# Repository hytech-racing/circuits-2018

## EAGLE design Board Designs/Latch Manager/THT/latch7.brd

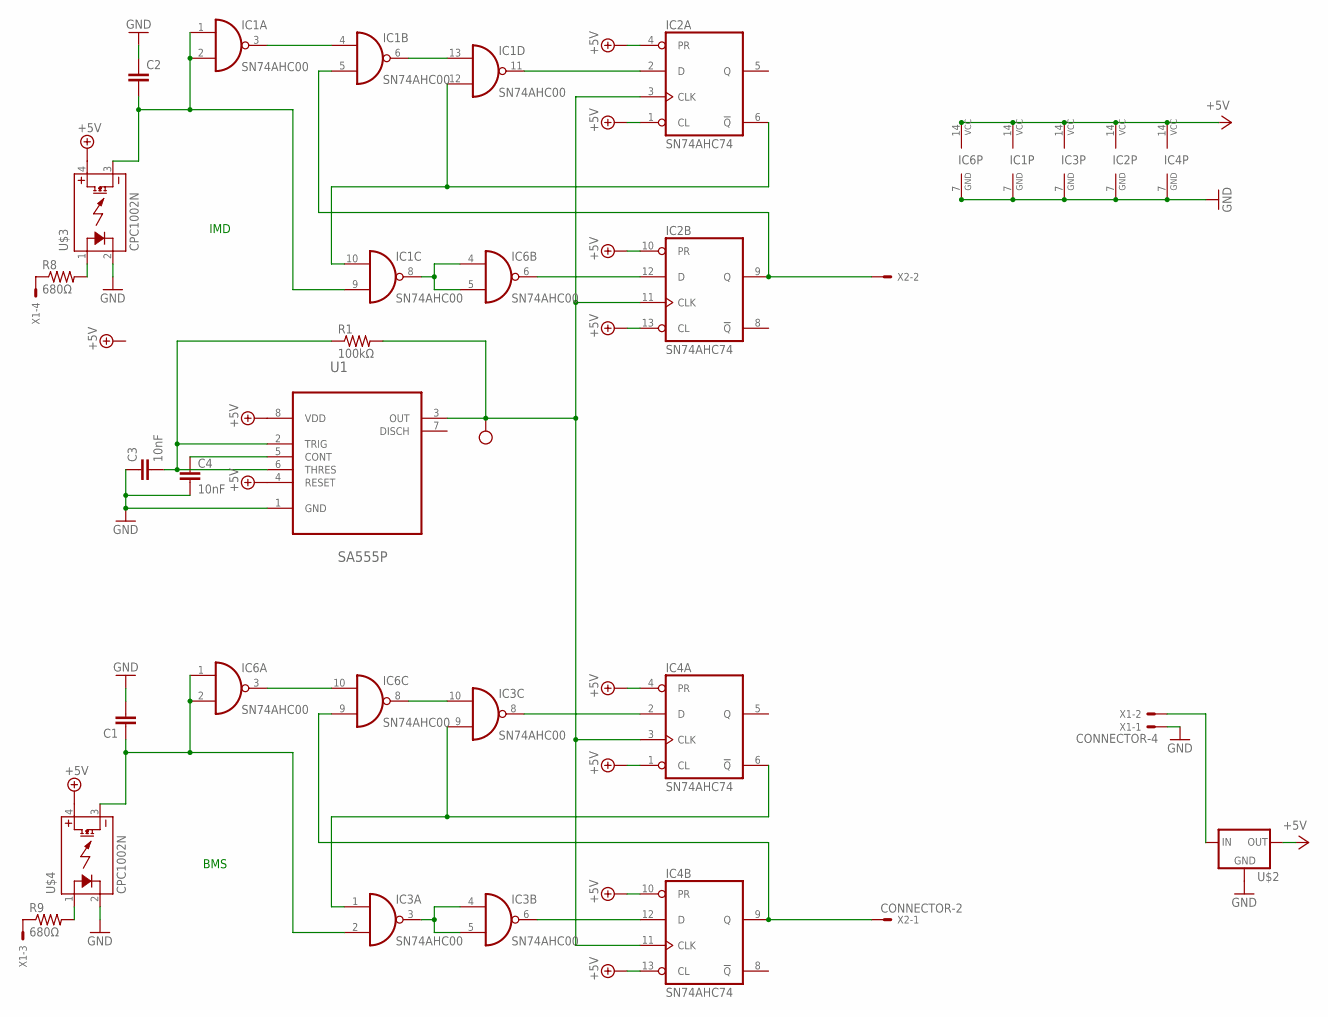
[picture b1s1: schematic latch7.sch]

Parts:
C1, C2: CAP_; AXIAL-5MM
C3, C4: 10nF; AXIAL-5MM
IC1, IC3, IC6: SN74AHC00; DIL14
IC2, IC4: SN74AHC74; DIL14
R1: 100kΩ; AXIAL-0.4
R8, R9: 680Ω; AXIAL-0.4
U1: SA555P; DIP254P762X508-8
U$1: TEST_POINT
U$2: 5VREG_LM340-NLM340T-5.0/NOPB; TO-220
U$3, U$4: CPC1002N; SOP04
X1: CONNECTOR-4; MINIFIT_5566-4
X2: CONNECTOR-2; MINIFIT_5566-2

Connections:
12V: U$2.1 (IN), X1.2
+5V: IC1.14 (VCC), IC2.1 (CL), IC2.4 (PR), IC2.10 (PR), IC2.13 (CL), IC2.14 (VCC), IC3.14 (VCC), IC4.1 (CL), IC4.4 (PR), IC4.10 (PR), IC4.13 (CL), IC4.14 (VCC), IC6.14 (VCC), U1.4 (RESET), U1.8 (VDD), U$2.3 (OUT), U$3.4 (DC+), U$4.4 (DC+)
BMS_5V: C1.P$1 (1), IC3.2 (I1), IC6.1 (I0), IC6.2 (I1), U$4.3 (DC-)
BMS_IN: R9.P$2 (2), U$4.1 (CONTROL+)
BMS_OUT: IC4.9 (Q), IC6.9 (I1), X2.1
CLK: IC2.3 (CLK), IC2.11 (CLK), IC4.3 (CLK), IC4.11 (CLK), R1.P$2 (2), U1.3 (OUT), U$1.P$1
GND: C1.P$2 (2), C2.P$1 (1), C3.P$1 (1), C4.P$2 (2), IC1.7 (GND), IC2.7 (GND), IC3.7 (GND), IC4.7 (GND), IC6.7 (GND), U1.1 (GND), U$2.2 (GND), U$3.2 (CONTROL-), U$4.2 (CONTROL-), X1.1
IMD_5V: C2.P$2 (2), IC1.1 (I0), IC1.2 (I1), IC1.9 (I1), U$3.3 (DC-)
IMD_IN: R8.P$2 (2), U$3.1 (CONTROL+)
IMD_OUT: IC1.5 (I1), IC2.9 (Q), X2.2
unnamed: IC1.3 (O), IC1.4 (I0)
unnamed: C3.P$2 (2), R1.P$1 (1), U1.2 (TRIG), U1.6 (THRES)
unnamed: IC1.6 (O), IC1.13 (I0)
unnamed: IC1.10 (I0), IC1.12 (I1), IC2.6 (!Q)
unnamed: IC1.11 (O), IC2.2 (D)
unnamed: C4.P$1 (1), U1.5 (CONT)
unnamed: IC2.12 (D), IC6.6 (O)
unnamed: IC3.6 (O), IC4.12 (D)
unnamed: IC1.8 (O), IC6.4 (I0), IC6.5 (I1)
unnamed: IC6.3 (O), IC6.10 (I0)
unnamed: IC3.10 (I0), IC6.8 (O)
unnamed: IC3.1 (I0), IC3.9 (I1), IC4.6 (!Q)
unnamed: IC3.8 (O), IC4.2 (D)
unnamed: IC3.3 (O), IC3.4 (I0), IC3.5 (I1)
unnamed: R8.P$1 (1), X1.4
unnamed: R9.P$1 (1), X1.3

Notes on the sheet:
IMD
BMS

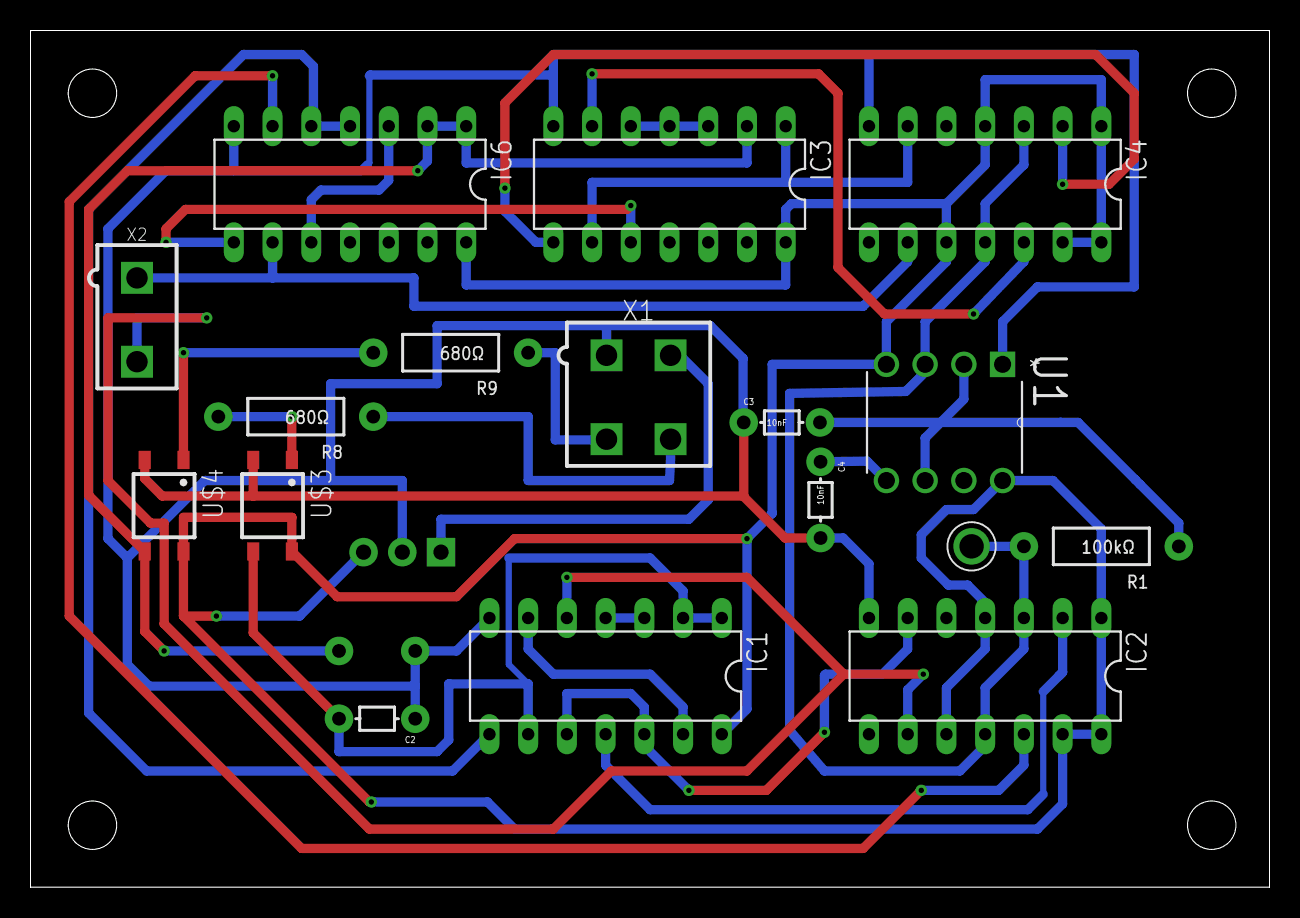
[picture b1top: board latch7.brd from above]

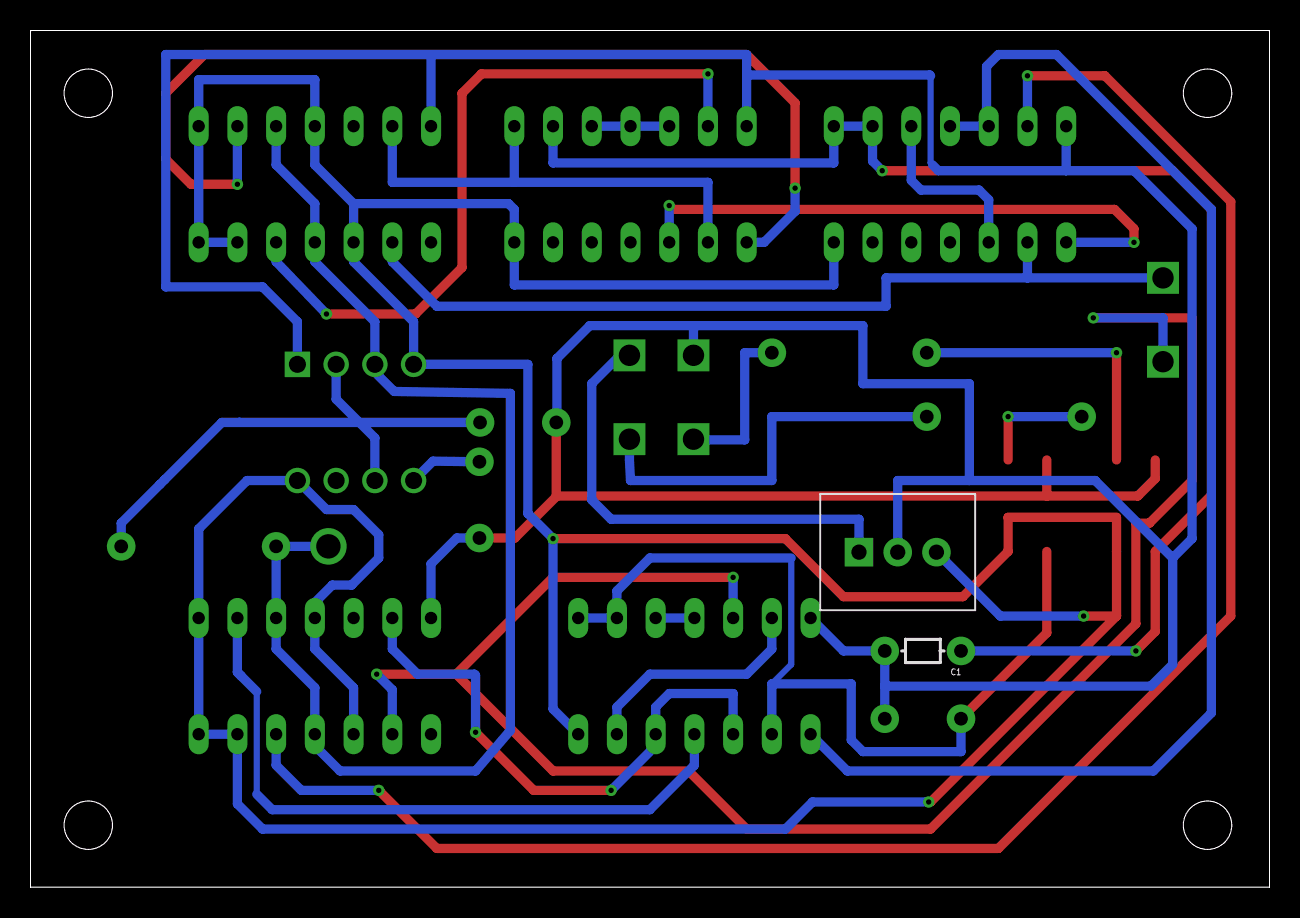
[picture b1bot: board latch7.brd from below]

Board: 2 copper layers, 81.3 x 56.2 mm, 19 parts (2 on the bottom side), 26 nets.

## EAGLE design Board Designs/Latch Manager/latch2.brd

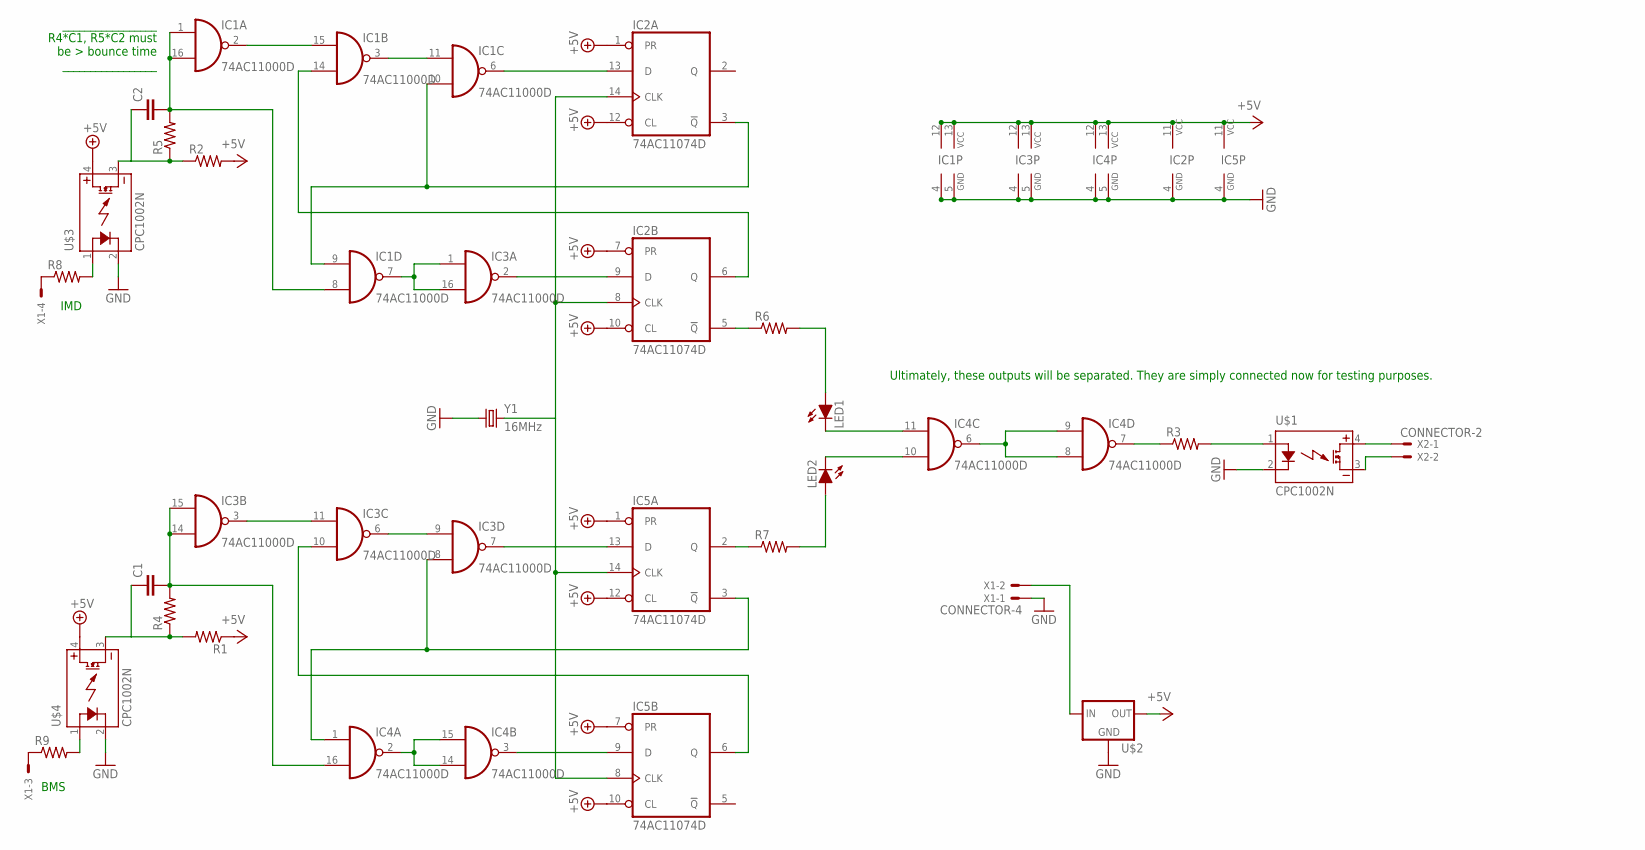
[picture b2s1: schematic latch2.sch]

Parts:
C1, C2: CAP0402-CAP; 0402-CAP
IC1, IC3, IC4: 74AC11000D; SO16
IC2, IC5: 74AC11074D; SO14
LED1, LED2: LED-0805; LED-805
R1, R2, R3, R4, R5, R6, R7, R8, R9: RESISTOR0402; 0402-RES
U$1, U$3, U$4: CPC1002N; SOP04
U$2: 5VREG_LM340-NLM340MPX-5.0/NOPB; SOT223
X1: CONNECTOR-4; MINIFIT_5566-4
X2: CONNECTOR-2; MINIFIT_5566-2
Y1: 16MHz; CRYSTAL-SMD-3.2X1.5MM

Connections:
+5V: IC1.12 (VCC), IC1.13 (VCC), IC2.1 (PR), IC2.7 (PR), IC2.10 (CL), IC2.11 (VCC), IC2.12 (CL), IC3.12 (VCC), IC3.13 (VCC), IC4.12 (VCC), IC4.13 (VCC), IC5.1 (PR), IC5.7 (PR), IC5.10 (CL), IC5.11 (VCC), IC5.12 (CL), R1.1, R2.2, U$2.3 (OUT), U$3.4 (DC+), U$4.4 (DC+)
GND: IC1.4 (GND), IC1.5 (GND), IC2.4 (GND), IC3.4 (GND), IC3.5 (GND), IC4.4 (GND), IC4.5 (GND), IC5.4 (GND), U$1.2 (CONTROL-), U$2.2 (GND), U$2.4 (GND), U$3.2 (CONTROL-), U$4.2 (CONTROL-), X1.1, Y1.P$1 (1)
unnamed: C2.1, R2.1, R5.1, U$3.3 (DC-)
unnamed: IC1.2 (O), IC1.15 (I0)
unnamed: C2.2, IC1.1 (I0), IC1.8 (I1), IC1.16 (I1), R5.2
unnamed: IC1.3 (O), IC1.11 (I0)
unnamed: IC1.9 (I0), IC1.10 (I1), IC2.3 (!Q)
unnamed: IC1.6 (O), IC2.13 (D)
unnamed: IC2.8 (CLK), IC2.14 (CLK), IC5.8 (CLK), IC5.14 (CLK), Y1.P$2 (2)
unnamed: IC2.9 (D), IC3.2 (O)
unnamed: IC1.14 (I1), IC2.6 (Q)
unnamed: IC4.3 (O), IC5.9 (D)
unnamed: IC1.7 (O), IC3.1 (I0), IC3.16 (I1)
unnamed: IC4.7 (O), R3.1
unnamed: R3.2, U$1.1 (CONTROL+)
unnamed: C1.2, IC3.14 (I1), IC3.15 (I0), R4.2
unnamed: C1.1, R1.2, R4.1, U$4.3 (DC-)
unnamed: U$2.1 (IN), X1.2
unnamed: U$1.4 (DC+), X2.1
unnamed: U$1.3 (DC-), X2.2
unnamed: IC3.3 (O), IC3.11 (I0)
unnamed: IC3.6 (O), IC3.9 (I0)
unnamed: IC3.8 (I1), IC4.1 (I0), IC5.3 (!Q)
unnamed: IC3.7 (O), IC5.13 (D)
unnamed: IC3.10 (I1), IC5.6 (Q)
unnamed: IC4.2 (O), IC4.14 (I1), IC4.15 (I0)
unnamed: LED2.A, R7.2
unnamed: IC4.6 (O), IC4.8 (I1), IC4.9 (I0)
unnamed: LED1.A, R6.2
unnamed: IC2.5 (!Q), R6.1
unnamed: IC5.2 (Q), R7.1
unnamed: R8.2, U$3.1 (CONTROL+)
unnamed: R8.1, X1.4
unnamed: R9.1, X1.3
unnamed: R9.2, U$4.1 (CONTROL+)
unnamed: IC4.11 (I0), LED1.C
unnamed: IC4.10 (I1), LED2.C

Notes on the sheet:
_________________ R4*C1, R5*C2 must be > bounce time _________________
IMD
BMS
Ultimately, these outputs will be separated. They are simply connected now for testing purposes.

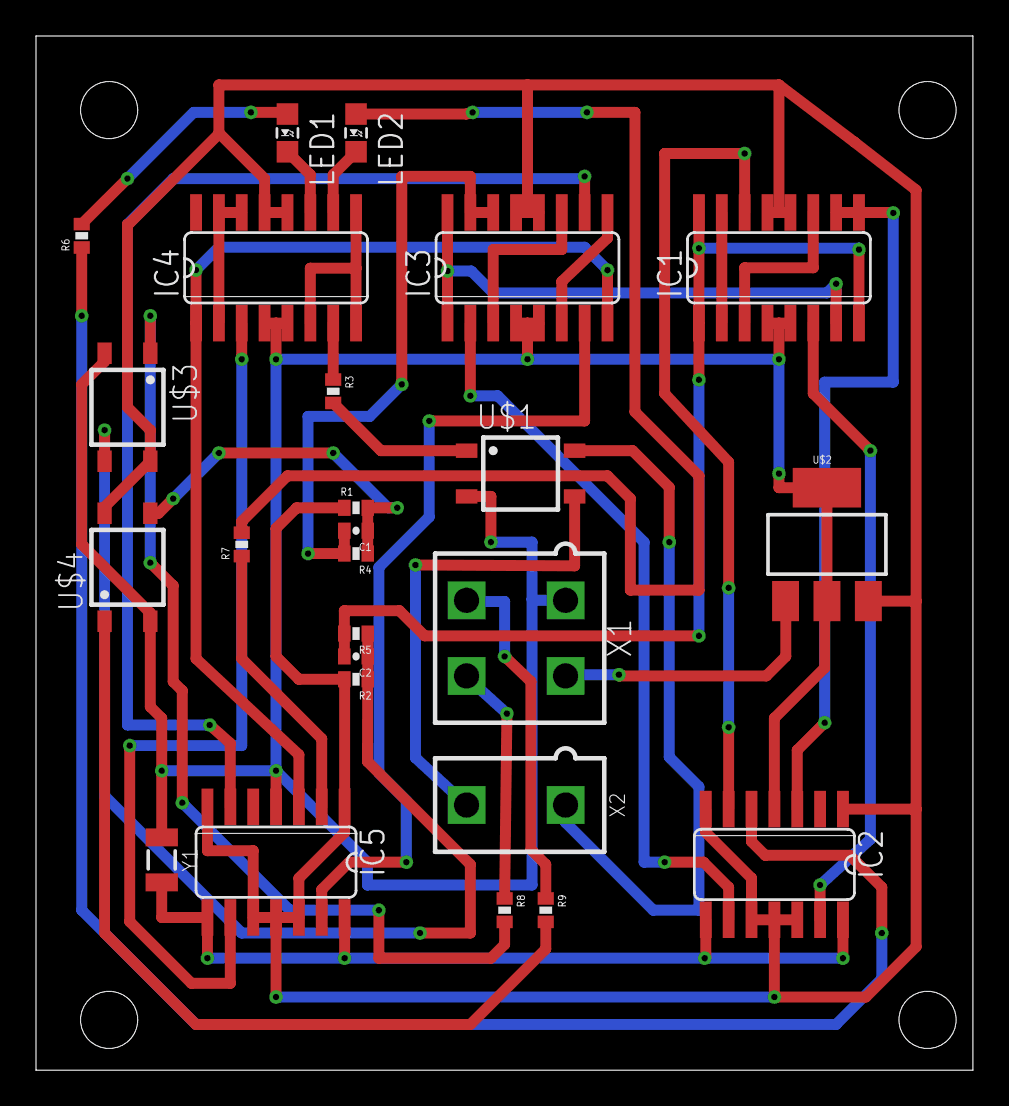
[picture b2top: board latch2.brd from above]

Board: 2 copper layers, 52.1 x 57.5 mm, 25 parts (0 on the bottom side), 37 nets.

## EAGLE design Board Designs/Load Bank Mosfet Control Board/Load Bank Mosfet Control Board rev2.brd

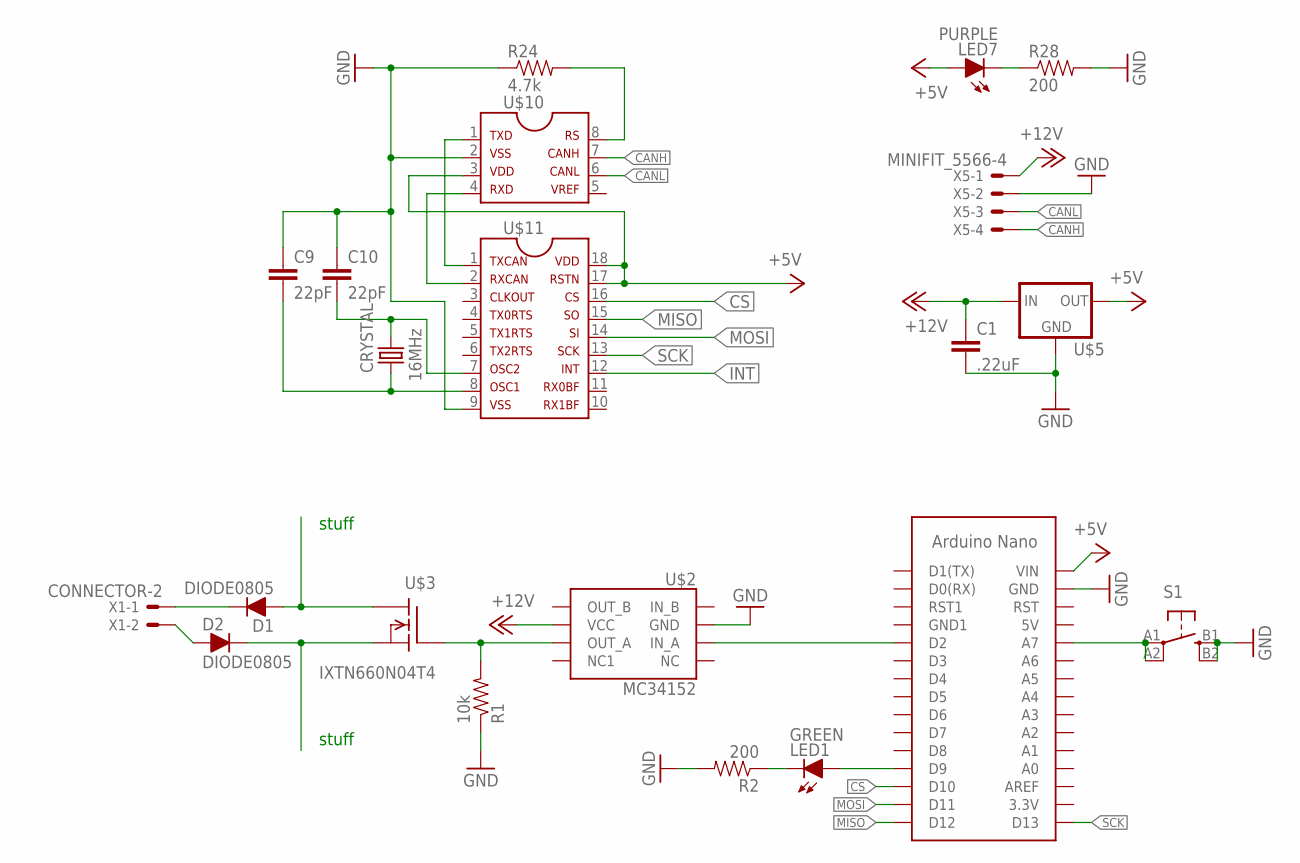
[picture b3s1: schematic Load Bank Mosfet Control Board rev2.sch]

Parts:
C1: .22uF; 0805
C9, C10: 22pF; 0805
CRYSTAL: 16MHz; HC49UP
D1, D2: DIODE0805; 0805_D
LED1: GREEN; LED-805
LED7: PURPLE; LED-805
R1: 10k; 0805
R2, R28: 200; 0805
R24: 4.7k; 0805
S1: BTN_10-XXSMD; TACTILE_SWITCH_SMD_6.2MM_TALL
U$2: MC34152; SOIC-08
U$3: IXTN660N04T4; SOT-227B
U$4: ARDUINO_NANO
U$5: 5VREG_LM340-NLM340MPX-5.0/NOPB; SOT223
U$10: MCP2551; SOIC-08
U$11: MCP2515SMD; SOIC-18W
X1: CONNECTOR-2; MINIFIT_5566-2
X5: MINIFIT_5566-4

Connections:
+5V: LED7.A, U$4.VIN, U$5.3 (OUT), U$10.3, U$11.17, U$11.18
+12V: C1.1, U$2.6 (VCC), U$5.1 (IN), X5.1
CANH: U$10.7, X5.4
CANL: U$10.6, X5.3
CS: U$4.D10, U$11.16
GND: C1.2, C9.1, C10.1, R1.1, R2.2, R24.1, R28.2, S1.B1 (S), S1.B2 (S1), U$2.3 (GND), U$4.GND, U$5.2 (GND), U$5.4 (GND), U$10.2, U$11.9, X5.2
INT: U$11.12
MISO: U$4.D12, U$11.15
MOSI: U$4.D11, U$11.14
unnamed: D1.C, X1.1
unnamed: D1.A, U$3.P$1 (D)
unnamed: R1.2, U$2.7 (OUT_A), U$3.P$4 (G)
unnamed: U$2.2 (IN_A), U$4.D2
unnamed: D2.C, U$3.P$2 (S), U$3.P$3 (S)
unnamed: LED1.A, U$4.D9
unnamed: D2.A, X1.2
unnamed: LED1.C, R2.1
unnamed: S1.A1, S1.A2 (P1), U$4.A7
unnamed: U$10.1, U$11.1
unnamed: U$10.4, U$11.2
unnamed: C9.2, CRYSTAL.2, U$11.8
unnamed: R24.2, U$10.8
unnamed: C10.2, CRYSTAL.1, U$11.7
unnamed: LED7.C, R28.1
SCK: U$4.D13, U$11.13

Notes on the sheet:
stuff

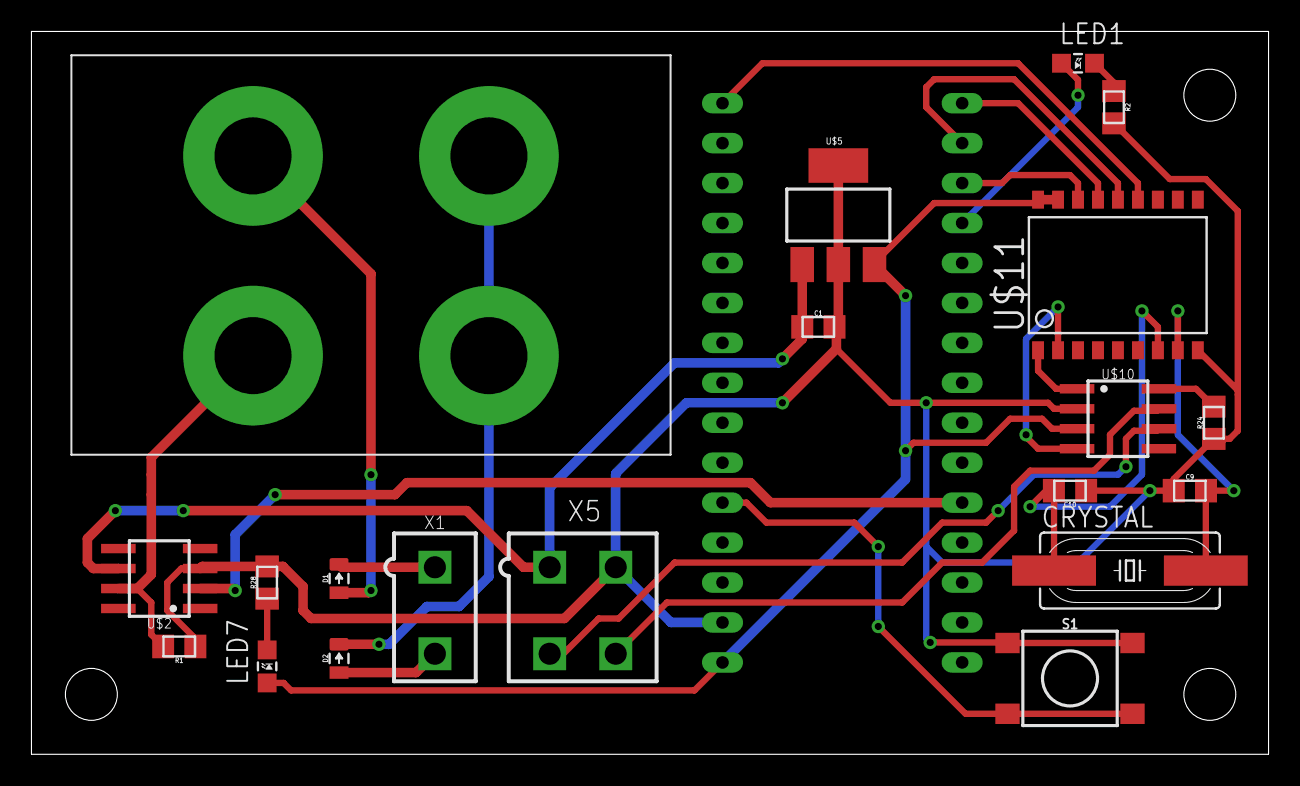
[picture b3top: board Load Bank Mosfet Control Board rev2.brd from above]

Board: 2 copper layers, 78.7 x 46.0 mm, 21 parts (0 on the bottom side), 24 nets.

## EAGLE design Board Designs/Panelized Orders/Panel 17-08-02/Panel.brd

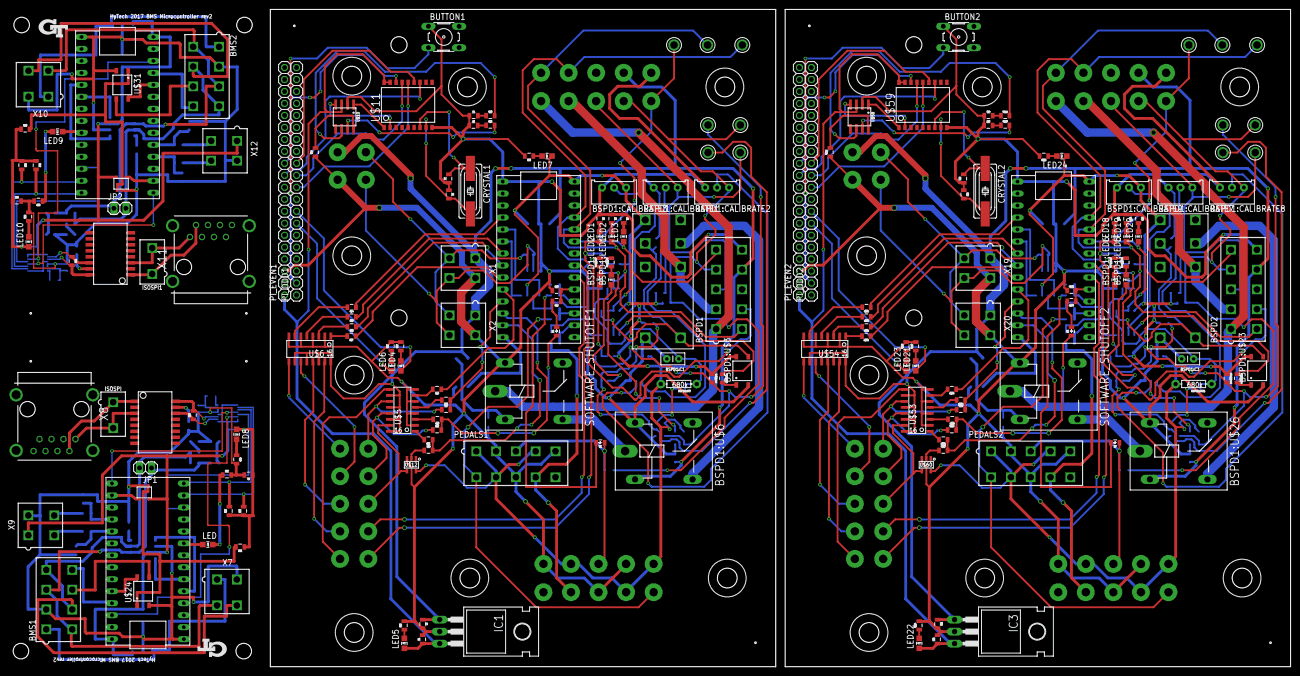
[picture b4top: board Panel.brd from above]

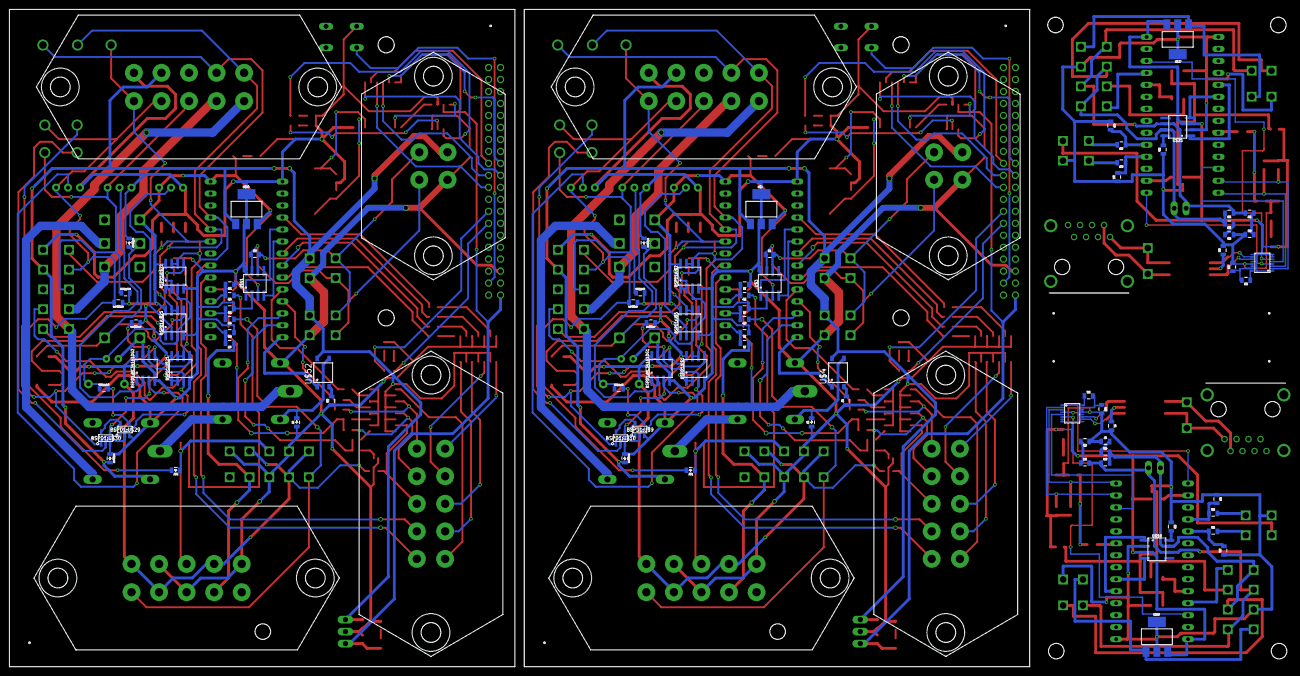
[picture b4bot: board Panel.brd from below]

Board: 2 copper layers, 270.5 x 139.4 mm, 278 parts (90 on the bottom side), 258 nets.

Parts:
BMS1, BMS2: MINIFIT_5566-8
BSPD1, BSPD2: MINIFIT_5566-10
BSPD1:C1, BSPD1:C3: .47u; CAP-PTH-SMALLEZ
BSPD1:CALIBRATE1, BSPD1:CALIBRATE2, BSPD1:CALIBRATE3, BSPD1:CALIBRATE7, BSPD1:CALIBRATE8, BSPD1:CALIBRATE9: TRIMPOT_3296
BSPD1:D1, BSPD1:D2, BSPD1:D5, BSPD1:D6: DIODE0805; 0805_D
BSPD1:LED1, BSPD1:LED2, BSPD1:LED5, BSPD1:LED6: LED-805
BSPD1:MC34161DG1, BSPD1:MC34161DG2: SOIC-08
BSPD1:R1, BSPD1:R5, BSPD1:R6, BSPD1:R7, BSPD1:R19, BSPD1:R23, BSPD1:R24, BSPD1:R25: 10k; 0805
BSPD1:R2, BSPD1:R8, BSPD1:R9, BSPD1:R20, BSPD1:R26, BSPD1:R27: 330; 0805
BSPD1:R3, BSPD1:R21: 680k; AXIAL-0.3EZ
BSPD1:R4, BSPD1:R22: 680; 0805
BSPD1:U$1, BSPD1:U$2, BSPD1:U$5, BSPD1:U$21, BSPD1:U$22, BSPD1:U$25: MCP6002SOIC; SOIC-08
BSPD1:U$3, BSPD1:U$23: CPC1002N; SOP04
BSPD1:U$4, BSPD1:U$24: JW2SN-DC5V; JW2SN
BSPD1:U$6, BSPD1:U$26: G5LE; ZF112
BSPD1:U$7, BSPD1:U$8, BSPD1:U$27, BSPD1:U$28: TEST_POINT
BSPD1:U$9, BSPD1:U$29: SN74AHC1G09; SOT-23-5
BSPD1:U$10, BSPD1:U$30: SN74LVC1G08; SOT-23-5
BUTTON1, BUTTON2: B3F-10XX
C1, C21: .1uF; 0805
C2, C22: .33uF; 0805
C3, C4, C9, C10, C13, C14, C23, C24: 560pF; 0805
C5, C11: 0.1uF; 0805
C6, C7, C25, C26: 22pF; 0805
C8, C12: 27pF; 0805
CRYSTAL1, CRYSTAL2: 16MHz; HC49UP
D1, D2, D3, D7, D8, D9: DIODE0805; 0805_D
IC1, IC3: TO-220-H
ISOSPI, ISOSPI1: CONNECTOR-2; MINIFIT_5566-2
JMP1, JMP2: DIODE0805; 0805_D
JP1, JP2: M02; 1X02
LED, LED1, LED2, LED3, LED4, LED5, LED6, LED7, LED8, LED9, LED10, LED18, LED19, LED20, LED21, LED22, LED23, LED24: LED-805
PEDALS1, PEDALS2: MINIFIT_5566-10
PI_EVEN1, PI_EVEN2: 1X20
PI_ODD1, PI_ODD2: 1X20
R1, R29, R39, R45, R55, R89: 120; 0805
R2, R3, R4, R90, R91, R92: 15k; 0805
R5, R6, R7, R25, R26, R27, R28, R93, R94, R95, R113, R114, R115, R116: 150; 0805
R8, R22, R23, R34, R35, R50, R51, R96, R110, R111: 100; 0805
R9, R10, R11, R97, R98, R99: 10k; 0805
R12, R100: 43k; 0805
R13, R101: 12k; 0805
R14, R15, R16, R17, R18, R19, R20, R21, R102, R103, R104, R105, R106, R107, R108, R109: 270; 0805
R24, R112: 4.7k; 0805
R30, R32, R43, R44, R46, R48, R59, R60: 2k; 0805
R31, R36, R40, R41, R42, R47, R52, R56, R57, R58: 1k; 0805
R33, R49: 68; 0805
R37, R38, R53, R54: 0805
SOFTWARE_SHUTOFF1, SOFTWARE_SHUTOFF2: G5LE; ZF112
U$1, U$23, U$30, U$49: TEENSY_3.2_SIMPLE
U$2, U$20, U$27, U$50: SOT223
U$3, U$10, U$18, U$25, U$51, U$58: MCP2551; SOIC-08
U$4, U$24, U$31, U$52: CPC1002N; SOP04
U$5, U$6, U$53, U$54: TLP291-4; SOIC-16
U$7, U$8, U$9, U$55, U$56, U$57: JUMPER; 0805
U$11, U$59: MCP2515SMD; SOIC-18W
U$12, U$60: SN74LV1T34; SOT-23-5
U$13, U$14, U$15, U$16, U$17, U$61, U$62, U$63, U$64, U$65: TEST_POINT
U$19, U$26: HX1188NLHX1188NL; HX1188NL
U$21, U$28: STWD100; SOT23-5
U$22, U$29: LTC6820; MSOP-16
X1, X2, X19, X20: MINIFIT_5566-4
X3, X21: CONNECTOR-4MX150L_VERTICAL-4; MX150L_VERTICAL-4
X4, X5, X6, X22, X23, X24: CONNECTOR-10MX150L_VERTICAL-10; MX150L_VERTICAL-10
X7, X9, X10, X12: CONNECTOR-4; MINIFIT_5566-4
X8, X11: RJ45-6L21-B; RJ45-SHIELD1

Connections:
12V_SUPPLY: BMS1.1, U$20.1, X7.1
12V_SUPPLY1: BMS2.1, U$27.1, X10.1
+5V1: C5.1, LED8.A, R30.1, R32.1, R33.1, U$18.3, U$20.3, U$21.VCC, U$22.1, U$22.7, U$22.8, U$22.9, U$22.12, U$23.VIN, X9.1
+5V2: C11.1, LED10.A, R46.1, R48.1, R49.1, U$25.3, U$27.3, U$28.VCC, U$29.1, U$29.7, U$29.8, U$29.9, U$29.12, U$30.VIN, X12.1
+5V3: BSPD1:CALIBRATE3.1, BSPD1:MC34161DG1.8, BSPD1:R1.1, BSPD1:R3.P$2, BSPD1:R5.1, BSPD1:R6.2, BSPD1:R7.1, BSPD1:U$1.8, BSPD1:U$2.8, BSPD1:U$3.4, BSPD1:U$4.4, BSPD1:U$5.8, BSPD1:U$9.5, BSPD1:U$10.5, LED7.A, PEDALS1.1, PEDALS1.4, PEDALS1.7, U$1.VIN, U$2.3, U$3.3, U$12.5, X4.1, X4.4, X4.7
+5V4: BSPD1:CALIBRATE9.1, BSPD1:MC34161DG2.8, BSPD1:R19.1, BSPD1:R21.P$2, BSPD1:R23.1, BSPD1:R24.2, BSPD1:R25.1, BSPD1:U$21.8, BSPD1:U$22.8, BSPD1:U$23.4, BSPD1:U$24.4, BSPD1:U$25.8, BSPD1:U$29.5, BSPD1:U$30.5, LED24.A, PEDALS2.1, PEDALS2.4, PEDALS2.7, U$49.VIN, U$50.3, U$51.3, U$60.5, X22.1, X22.4, X22.7
+5V/1: C1.1, IC1.3, LED5.A, PI_EVEN1.1, U$10.3, U$11.17, U$11.18
+5V/3: C21.1, IC3.3, LED22.A, PI_EVEN2.1, U$58.3, U$59.17, U$59.18
+12V1: BSPD1.9, BSPD1:D2.C, BSPD1:U$6.2, C2.1, IC1.1, U$2.1, U$4.4, U$5.10, U$5.12, U$5.14, U$5.16, U$6.10, U$6.12, U$6.14, U$6.16, X1.1, X2.1, X3.1, X5.9
+12V2: BSPD1:D6.C, BSPD1:U$26.2, BSPD2.9, C22.1, IC3.1, U$50.1, U$52.4, U$53.10, U$53.12, U$53.14, U$53.16, U$54.10, U$54.12, U$54.14, U$54.16, X19.1, X20.1, X21.1, X23.9
BSPD1:N$1: BSPD1:CALIBRATE2.2, BSPD1:MC34161DG1.3
BSPD1:N$2: BSPD1:CALIBRATE1.2, BSPD1:MC34161DG1.2
BSPD1:N$3: BSPD1:R4.1, BSPD1:U$5.1
BSPD1:N$4: BSPD1:C1.1, BSPD1:R2.1, BSPD1:R3.P$1, BSPD1:U$2.3, BSPD1:U$5.3
BSPD1:N$5: BSPD1:CALIBRATE3.2, BSPD1:U$5.2
BSPD1:N$6: BSPD1:D1.C, BSPD1:U$3.3, BSPD1:U$4.3, BSPD1:U$4.COIL-, BSPD1:U$5.5
BSPD1:N$7: BSPD1:U$2.5, BSPD1:U$10.4
BSPD1:N$8: BSPD1:R2.2, BSPD1:U$9.4
BSPD1:N$9: BSPD1:R4.2, BSPD1:U$3.1
BSPD1:N$10: BSPD1:LED2.A, BSPD1:U$1.6, BSPD1:U$1.7
BSPD1:N$11: BSPD1:MC34161DG1.5, BSPD1:R1.2, BSPD1:U$1.5, BSPD1:U$7.P$1, BSPD1:U$9.1, BSPD1:U$10.1
BSPD1:N$12: BSPD1:MC34161DG1.6, BSPD1:R7.2, BSPD1:U$1.3, BSPD1:U$8.P$1, BSPD1:U$9.2, BSPD1:U$10.2
BSPD1:N$13: BSPD1:LED1.A, BSPD1:U$1.1, BSPD1:U$1.2
BSPD1:N$14: BSPD1:LED2.C, BSPD1:R9.1
BSPD1:N$15: BSPD1:LED1.C, BSPD1:R8.1
BSPD1:N$31: BSPD1:CALIBRATE8.2, BSPD1:MC34161DG2.3
BSPD1:N$32: BSPD1:CALIBRATE7.2, BSPD1:MC34161DG2.2
BSPD1:N$33: BSPD1:R22.1, BSPD1:U$25.1
BSPD1:N$34: BSPD1:C3.1, BSPD1:R20.1, BSPD1:R21.P$1, BSPD1:U$22.3, BSPD1:U$25.3
BSPD1:N$35: BSPD1:CALIBRATE9.2, BSPD1:U$25.2
BSPD1:N$36: BSPD1:D5.C, BSPD1:U$23.3, BSPD1:U$24.3, BSPD1:U$24.COIL-, BSPD1:U$25.5
BSPD1:N$37: BSPD1:U$22.5, BSPD1:U$30.4
BSPD1:N$38: BSPD1:R20.2, BSPD1:U$29.4
BSPD1:N$39: BSPD1:R22.2, BSPD1:U$23.1
BSPD1:N$40: BSPD1:LED6.A, BSPD1:U$21.6, BSPD1:U$21.7
BSPD1:N$41: BSPD1:MC34161DG2.5, BSPD1:R19.2, BSPD1:U$21.5, BSPD1:U$27.P$1, BSPD1:U$29.1, BSPD1:U$30.1
BSPD1:N$42: BSPD1:MC34161DG2.6, BSPD1:R25.2, BSPD1:U$21.3, BSPD1:U$28.P$1, BSPD1:U$29.2, BSPD1:U$30.2
BSPD1:N$43: BSPD1:LED5.A, BSPD1:U$21.1, BSPD1:U$21.2
BSPD1:N$44: BSPD1:LED6.C, BSPD1:R27.1
BSPD1:N$45: BSPD1:LED5.C, BSPD1:R26.1
BSPD1:SHUTDOWN_C1: BSPD1:U$4.6, BSPD1:U$6.S
BSPD1:SHUTDOWN_C2: BSPD1:U$24.6, BSPD1:U$26.S
BUT1: BUTTON1.3, PI_ODD1.2
BUT2: BUTTON2.3, PI_ODD2.2
CAN-H1: R22.2, U$10.7
CAN-H2: R110.2, U$58.7
CAN-L1: R23.2, U$10.6
CAN-L2: R111.2, U$58.6
CANH: BMS1.4, BMS1.6, JP1.2, R29.2, R34.2, U$18.7, X7.4
CANH1: BMS2.4, BMS2.6, JP2.2, R45.2, R50.2, U$25.7, X10.4
CANL: BMS1.3, BMS1.5, JP1.1, R29.1, R35.2, U$18.6, X7.3
CANL1: BMS2.3, BMS2.5, JP2.1, R45.1, R51.2, U$25.6, X10.3
CS1: PI_EVEN1.12, U$11.16
CS2: PI_EVEN2.12, U$59.16
GND1: BMS1.2, C5.2, C8.2, C9.1, C10.1, R31.2, R36.1, R37.2, R38.2, R43.1, R44.1, U$18.2, U$20.2, U$20.4, U$21.EN, U$21.GND, U$22.13, U$22.14, U$23.GND, U$24.2, X7.2, X9.2
GND2: BMS2.2, C11.2, C12.2, C13.1, C14.1, R47.2, R52.1, R53.2, R54.2, R59.1, R60.1, U$25.2, U$27.2, U$27.4, U$28.EN, U$28.GND, U$29.13, U$29.14, U$30.GND, U$31.2, X10.2, X12.2
GND3: BSPD1.10, BSPD1:C1.2, BSPD1:CALIBRATE1.3, BSPD1:CALIBRATE2.3, BSPD1:CALIBRATE3.3, BSPD1:D1.A, BSPD1:D2.A, BSPD1:MC34161DG1.4, BSPD1:MC34161DG1.7, BSPD1:R8.2, BSPD1:R9.2, BSPD1:U$1.4, BSPD1:U$2.4, BSPD1:U$3.2, BSPD1:U$4.COIL+, BSPD1:U$5.4, BSPD1:U$6.1, BSPD1:U$9.3, BSPD1:U$10.3, BUTTON1.1, C1.2, C2.2, C3.1, C4.1, C6.1, C7.1, D3.A, IC1.2, PEDALS1.2, PEDALS1.5, PEDALS1.8, PI_EVEN1.3, R2.1, R3.1, R4.1, R5.1, R6.1, R7.1, R8.1, R13.1, R24.1, R25.2, R26.2, R27.2, R28.2, SOFTWARE_SHUTOFF1.1, U$1.GND, U$2.2, U$2.4, U$3.2, U$3.8, U$5.2, U$5.4, U$5.6, U$5.8, U$6.2, U$6.4, U$6.6, U$6.8, U$10.2, U$11.9, U$12.3, X1.2, X2.2, X3.2, X4.2, X4.5, X4.8, X5.10
GND4: BSPD1:C3.2, BSPD1:CALIBRATE7.3, BSPD1:CALIBRATE8.3, BSPD1:CALIBRATE9.3, BSPD1:D5.A, BSPD1:D6.A, BSPD1:MC34161DG2.4, BSPD1:MC34161DG2.7, BSPD1:R26.2, BSPD1:R27.2, BSPD1:U$21.4, BSPD1:U$22.4, BSPD1:U$23.2, BSPD1:U$24.COIL+, BSPD1:U$25.4, BSPD1:U$26.1, BSPD1:U$29.3, BSPD1:U$30.3, BSPD2.10, BUTTON2.1, C21.2, C22.2, C23.1, C24.1, C25.1, C26.1, D9.A, IC3.2, PEDALS2.2, PEDALS2.5, PEDALS2.8, PI_EVEN2.3, R90.1, R91.1, R92.1, R93.1, R94.1, R95.1, R96.1, R101.1, R112.1, R113.2, R114.2, R115.2, R116.2, SOFTWARE_SHUTOFF2.1, U$49.GND, U$50.2, U$50.4, U$51.2, U$51.8, U$53.2, U$53.4, U$53.6, U$53.8, U$54.2, U$54.4, U$54.6, U$54.8, U$58.2, U$59.9, U$60.3, X19.2, X20.2, X21.2, X22.2, X22.5, X22.8, X23.10
INT1: PI_EVEN1.11, U$11.12
INT2: PI_EVEN2.11, U$59.12
ISOSPI-M: ISOSPI.2, U$19.3, X8.1
ISOSPI-M1: ISOSPI1.2, U$26.3, X11.1
ISOSPI-P: ISOSPI.1, U$19.1, X8.2
ISOSPI-P1: ISOSPI1.1, U$26.1, X11.2
LED1: LED6.A, PI_ODD1.7
LED2: LED4.A, PI_ODD1.8
LED5: LED23.A, PI_ODD2.7
LED6: LED21.A, PI_ODD2.8
MISO1: R32.2, U$22.3, U$23.D12
MISO2: R48.2, U$29.3, U$30.D12
MISO3: PI_ODD1.11, U$11.15
MISO4: PI_ODD2.11, U$59.15
MOSI1: R30.2, U$22.2, U$23.D11
MOSI2: R46.2, U$29.2, U$30.D11
MOSI3: PI_ODD1.10, U$11.14
MOSI4: PI_ODD2.10, U$59.14
unnamed: R1.2, U$3.6, X1.3, X2.3, X3.3
unnamed: R1.1, U$3.7, X1.4, X2.4, X3.4
unnamed: U$1.D4(CANRX), U$3.4
unnamed: U$1.D3(CANTX), U$3.1
unnamed: PEDALS1.6, R10.1, X4.6
unnamed: R2.2, R9.2, U$1.A0
unnamed: LED1.C, R5.2
unnamed: LED2.C, R6.2
unnamed: LED3.C, R7.2
unnamed: R8.2, U$4.2
unnamed: R3.2, R10.2, U$1.A1
unnamed: PEDALS1.9, R9.1, X4.9
unnamed: R4.2, R11.2, U$1.A2
unnamed: D1.A, JMP1.A, PEDALS1.3, X4.3
unnamed: D1.C, R11.1
unnamed: D3.C, SOFTWARE_SHUTOFF1.2, U$4.3
unnamed: D2.C, R12.2
unnamed: R14.1, U$1.D2
unnamed: R15.1, U$1.D5
unnamed: R16.1, U$1.D6
unnamed: R17.1, U$1.D7(RX3)
unnamed: R19.1, U$1.D9(RX2), U$7.2
unnamed: U$6.9, X6.1
unnamed: U$6.11, X6.2
unnamed: U$6.13, X6.3
unnamed: U$6.15, X6.4
unnamed: U$5.9, X6.5
unnamed: U$5.11, U$7.1, X6.6
unnamed: R14.2, U$6.7
unnamed: R15.2, U$6.5
unnamed: R16.2, U$6.3
unnamed: R17.2, U$6.1
unnamed: R18.1, U$1.D8(TX3)
unnamed: R18.2, U$5.7
unnamed: R19.2, U$5.5
unnamed: R20.1, U$1.D10(TX2), U$8.2
unnamed: R21.1, U$1.D11, U$9.2
unnamed: U$1.A5, X6.10
unnamed: U$1.A4, X6.9
unnamed: R20.2, U$5.3
unnamed: R21.2, U$5.1
unnamed: U$5.13, U$8.1, X6.7
unnamed: U$5.15, U$12.4, X6.8
unnamed: U$10.1, U$11.1
unnamed: U$10.4, U$11.2
unnamed: C6.2, CRYSTAL1.2, U$11.8
unnamed: R24.2, U$10.8
unnamed: C7.2, CRYSTAL1.1, U$11.7
unnamed: C3.2, R22.1
unnamed: C4.2, R23.1
unnamed: LED4.C, R25.1
unnamed: LED5.C, R26.1
unnamed: LED6.C, R27.1
unnamed: U$18.1, U$23.D3(CANTX)
unnamed: R36.2, U$18.8
unnamed: C9.2, R34.1
unnamed: C10.2, R35.1
unnamed: LED.C, R37.1
unnamed: LED8.C, R38.1
unnamed: R40.1, U$22.16
unnamed: R31.1, R40.2, U$22.15
unnamed: R39.1, U$19.14, U$22.10
unnamed: R39.2, U$19.16, U$22.11
unnamed: C8.1, U$19.15
unnamed: U$18.4, U$23.D4(CANRX)
unnamed: LED.A, U$23.D7(RX3)
unnamed: R33.2, U$21.WDO, U$24.1
unnamed: BMS1.7, U$24.3
unnamed: U$23.A8, U$24.4
unnamed: BMS1.8, U$23.A9
unnamed: R41.2, X9.3
unnamed: R41.1, R43.2, U$23.A3
unnamed: R42.2, X9.4
unnamed: R42.1, R44.2, U$23.A2
unnamed: U$21.WDI, U$23.A0
unnamed: U$22.6, U$23.3.3V
unnamed: U$22.5, U$23.D10(TX2)
unnamed: U$25.1, U$30.D3(CANTX)
unnamed: R52.2, U$25.8
unnamed: C13.2, R50.1
unnamed: C14.2, R51.1
unnamed: LED9.C, R53.1
unnamed: LED10.C, R54.1
unnamed: R56.1, U$29.16
unnamed: R47.1, R56.2, U$29.15
unnamed: R55.1, U$26.14, U$29.10
unnamed: R55.2, U$26.16, U$29.11
unnamed: C12.1, U$26.15
unnamed: U$25.4, U$30.D4(CANRX)
unnamed: LED9.A, U$30.D7(RX3)
unnamed: R49.2, U$28.WDO, U$31.1
unnamed: BMS2.7, U$31.3
unnamed: U$30.A8, U$31.4
unnamed: BMS2.8, U$30.A9
unnamed: R57.2, X12.3
unnamed: R57.1, R59.2, U$30.A3
unnamed: R58.2, X12.4
unnamed: R58.1, R60.2, U$30.A2
unnamed: U$28.WDI, U$30.A0
unnamed: U$29.6, U$30.3.3V
unnamed: U$29.5, U$30.D10(TX2)
unnamed: U$9.1, U$12.2
unnamed: LED7.C, R28.1
unnamed: R89.2, U$51.6, X19.3, X20.3, X21.3
unnamed: R89.1, U$51.7, X19.4, X20.4, X21.4
unnamed: U$49.D4(CANRX), U$51.4
unnamed: U$49.D3(CANTX), U$51.1
unnamed: PEDALS2.6, R98.1, X22.6
unnamed: R90.2, R97.2, U$49.A0
unnamed: LED18.C, R93.2
unnamed: LED19.C, R94.2
unnamed: LED20.C, R95.2
unnamed: R96.2, U$52.2
unnamed: R91.2, R98.2, U$49.A1
unnamed: PEDALS2.9, R97.1, X22.9
unnamed: R92.2, R99.2, U$49.A2
unnamed: D7.A, JMP2.A, PEDALS2.3, X22.3
unnamed: D7.C, R99.1
unnamed: D9.C, SOFTWARE_SHUTOFF2.2, U$52.3
unnamed: D8.C, R100.2
unnamed: R102.1, U$49.D2
unnamed: R103.1, U$49.D5
unnamed: R104.1, U$49.D6
unnamed: R105.1, U$49.D7(RX3)
unnamed: R107.1, U$49.D9(RX2), U$55.2
unnamed: U$54.9, X24.1
unnamed: U$54.11, X24.2
unnamed: U$54.13, X24.3
unnamed: U$54.15, X24.4
unnamed: U$53.9, X24.5
unnamed: U$53.11, U$55.1, X24.6
unnamed: R102.2, U$54.7
unnamed: R103.2, U$54.5
unnamed: R104.2, U$54.3
unnamed: R105.2, U$54.1
unnamed: R106.1, U$49.D8(TX3)
unnamed: R106.2, U$53.7
unnamed: R107.2, U$53.5
unnamed: R108.1, U$49.D10(TX2), U$56.2
unnamed: R109.1, U$49.D11, U$57.2
unnamed: U$49.A5, X24.10
unnamed: U$49.A4, X24.9
unnamed: R108.2, U$53.3
unnamed: R109.2, U$53.1
unnamed: U$53.13, U$56.1, X24.7
unnamed: U$53.15, U$60.4, X24.8
unnamed: U$58.1, U$59.1
unnamed: U$58.4, U$59.2
unnamed: C25.2, CRYSTAL2.2, U$59.8
unnamed: R112.2, U$58.8
unnamed: C26.2, CRYSTAL2.1, U$59.7
unnamed: C23.2, R110.1
unnamed: C24.2, R111.1
unnamed: LED21.C, R113.1
unnamed: LED22.C, R114.1
unnamed: LED23.C, R115.1
unnamed: U$57.1, U$60.2
unnamed: LED24.C, R116.1
READ_CHARGE1: BSPD1.6, BSPD1:U$2.1, BSPD1:U$2.2, LED2.A, U$1.A8, U$16.P$1, X5.6
READ_CHARGE2: BSPD1:U$22.1, BSPD1:U$22.2, BSPD2.6, LED19.A, U$49.A8, U$64.P$1, X23.6
READ_FAULT1: BSPD1.5, BSPD1:U$5.6, BSPD1:U$5.7, LED3.A, U$1.A7, U$15.P$1, X5.5
READ_FAULT2: BSPD1:U$25.6, BSPD1:U$25.7, BSPD2.5, LED20.A, U$49.A7, U$63.P$1, X23.5
READ_SWITCH1: BSPD1.7, BSPD1:U$2.6, BSPD1:U$2.7, LED1.A, U$1.A9, U$17.P$1, X5.7
READ_SWITCH2: BSPD1:U$22.6, BSPD1:U$22.7, BSPD2.7, LED18.A, U$49.A9, U$65.P$1, X23.7
READ_UPSTREAM_SHUTDOWN1: R12.1, R13.2, U$1.A3
READ_UPSTREAM_SHUTDOWN2: R100.1, R101.2, U$49.A3
SCK1: U$22.4, U$23.D13
SCK2: U$29.4, U$30.D13
SCK3: PI_ODD1.12, U$11.13
SCK4: PI_ODD2.12, U$59.13
SHUTDOWN_A1: BSPD1.1, D2.A, SOFTWARE_SHUTOFF1.P, X5.1
SHUTDOWN_A2: BSPD2.1, D8.A, SOFTWARE_SHUTOFF2.P, X23.1
SHUTDOWN_B1: BSPD1:U$6.P, SOFTWARE_SHUTOFF1.S
SHUTDOWN_B2: BSPD1:U$26.P, SOFTWARE_SHUTOFF2.S
SHUTDOWN_D1: BSPD1.2, BSPD1:U$4.7, X5.2
SHUTDOWN_D2: BSPD1:U$24.7, BSPD2.2, X23.2
SHUTDOWN_RELAY_CTRL1: U$1.D12, U$4.1
SHUTDOWN_RELAY_CTRL2: U$49.D12, U$52.1
SIGNAL_BRAKE1: BSPD1.4, BSPD1:CALIBRATE2.1, BSPD1:R5.2, JMP1.C, U$13.P$1, X5.4
SIGNAL_BRAKE2: BSPD1:CALIBRATE8.1, BSPD1:R23.2, BSPD2.4, JMP2.C, U$61.P$1, X23.4
SIGNAL_CURRENT1: BSPD1.3, BSPD1:CALIBRATE1.1, BSPD1:R6.1, U$14.P$1, X5.3
SIGNAL_CURRENT2: BSPD1:CALIBRATE7.1, BSPD1:R24.1, BSPD2.3, U$62.P$1, X23.3

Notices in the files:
parts and their libraries:
SparkFun-FreqCtrl: Licensing: Creative Commons ShareAlike 4.0 International - https://creativecommons.org/licenses/by-sa/4.0
